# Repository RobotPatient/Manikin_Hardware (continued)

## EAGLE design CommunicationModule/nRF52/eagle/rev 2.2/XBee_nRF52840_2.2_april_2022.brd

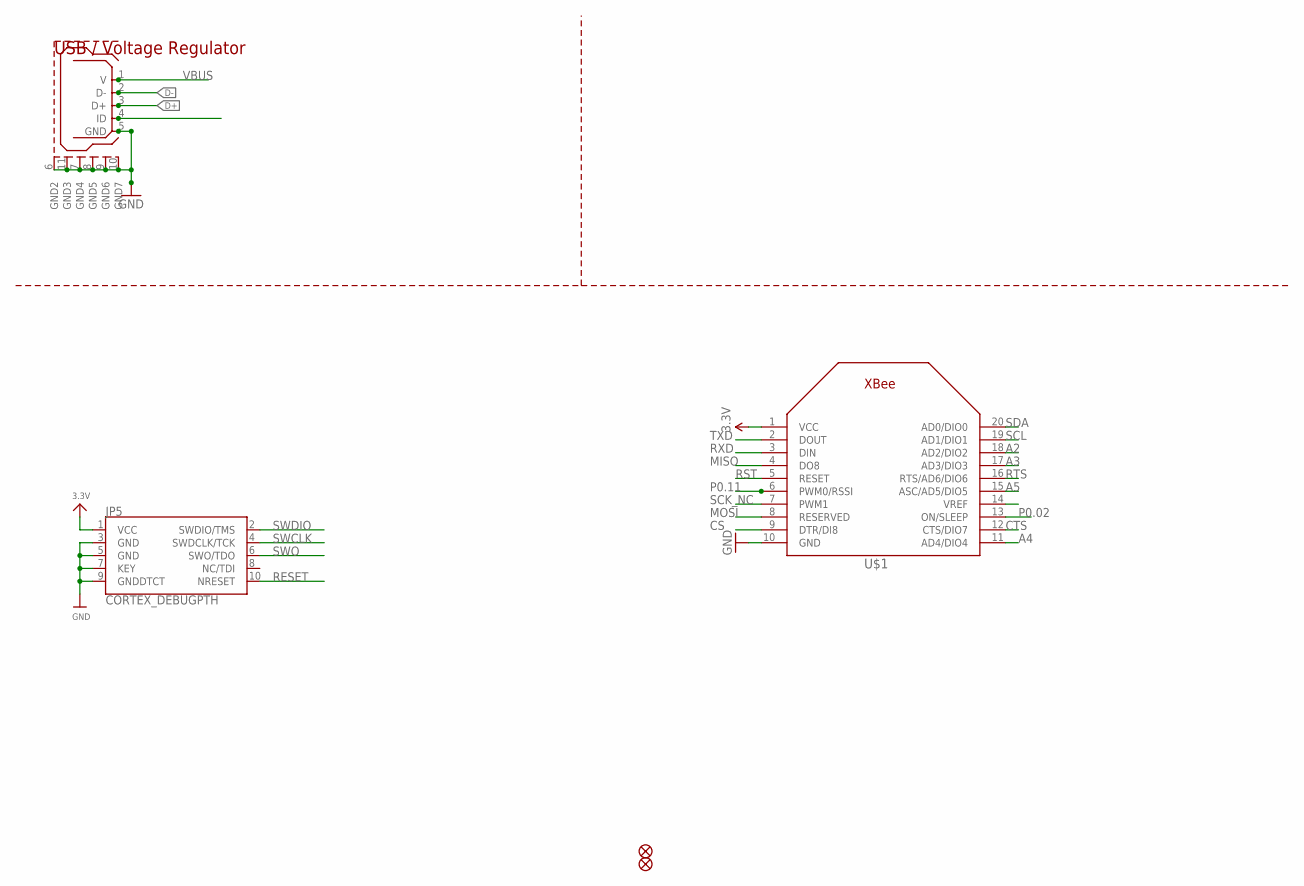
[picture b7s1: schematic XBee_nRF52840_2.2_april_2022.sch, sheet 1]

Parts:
FID1, FID3: FIDUCIAL_1MM
JP5: CORTEX_DEBUGPTH; 2X5-PTH-1.27MM
U$1: XBEE
U$2: USB_MICROB; USB_MICROB_PACKAGE

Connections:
3.3V: JP5.1 (VCC), U$1.1 (VCC); also elsewhere on the board
A2: U$1.18 (AD2/DIO2); also elsewhere on the board
A3: U$1.17 (AD3/DIO3); also elsewhere on the board
A4: U$1.11 (AD4/DIO4); also elsewhere on the board
A5: U$1.15 (ASC/AD5/DIO5); also elsewhere on the board
CS: U$1.9 (DTR/DI8)
CTS: U$1.12 (CTS/DIO7)
D+: U$2.3 (D+); also elsewhere on the board
D-: U$2.2 (D-); also elsewhere on the board
GND: JP5.3 (GND), JP5.5 (GND), JP5.7 (KEY), JP5.9 (GNDDTCT), U$1.10 (GND), U$2.5 (GND), U$2.6 (GND2), U$2.7 (GND4), U$2.8 (GND5), U$2.9 (GND6), U$2.10 (GND7), U$2.11 (GND3); also elsewhere on the board
MISO: U$1.4 (DO8); also elsewhere on the board
MOSI: U$1.8 (RESERVED); also elsewhere on the board
P0.02: U$1.13 (ON/SLEEP)
P0.11: U$1.6 (PWM0/RSSI)
RESET: JP5.10 (NRESET); also elsewhere on the board
RST: U$1.5 (RESET)
RTS: U$1.16 (RTS/AD6/DIO6)
RXD: U$1.3 (DIN); also elsewhere on the board
SCK_NC: U$1.7 (PWM1)
SCL: U$1.19 (AD1/DIO1); also elsewhere on the board
SDA: U$1.20 (AD0/DIO0); also elsewhere on the board
SWCLK: JP5.4 (SWDCLK/TCK); also elsewhere on the board
SWDIO: JP5.2 (SWDIO/TMS); also elsewhere on the board
SWO: JP5.6 (SWO/TDO); also elsewhere on the board
TXD: U$1.2 (DOUT); also elsewhere on the board
VBUS: U$2.1 (V); also elsewhere on the board

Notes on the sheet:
USB / Voltage Regulator

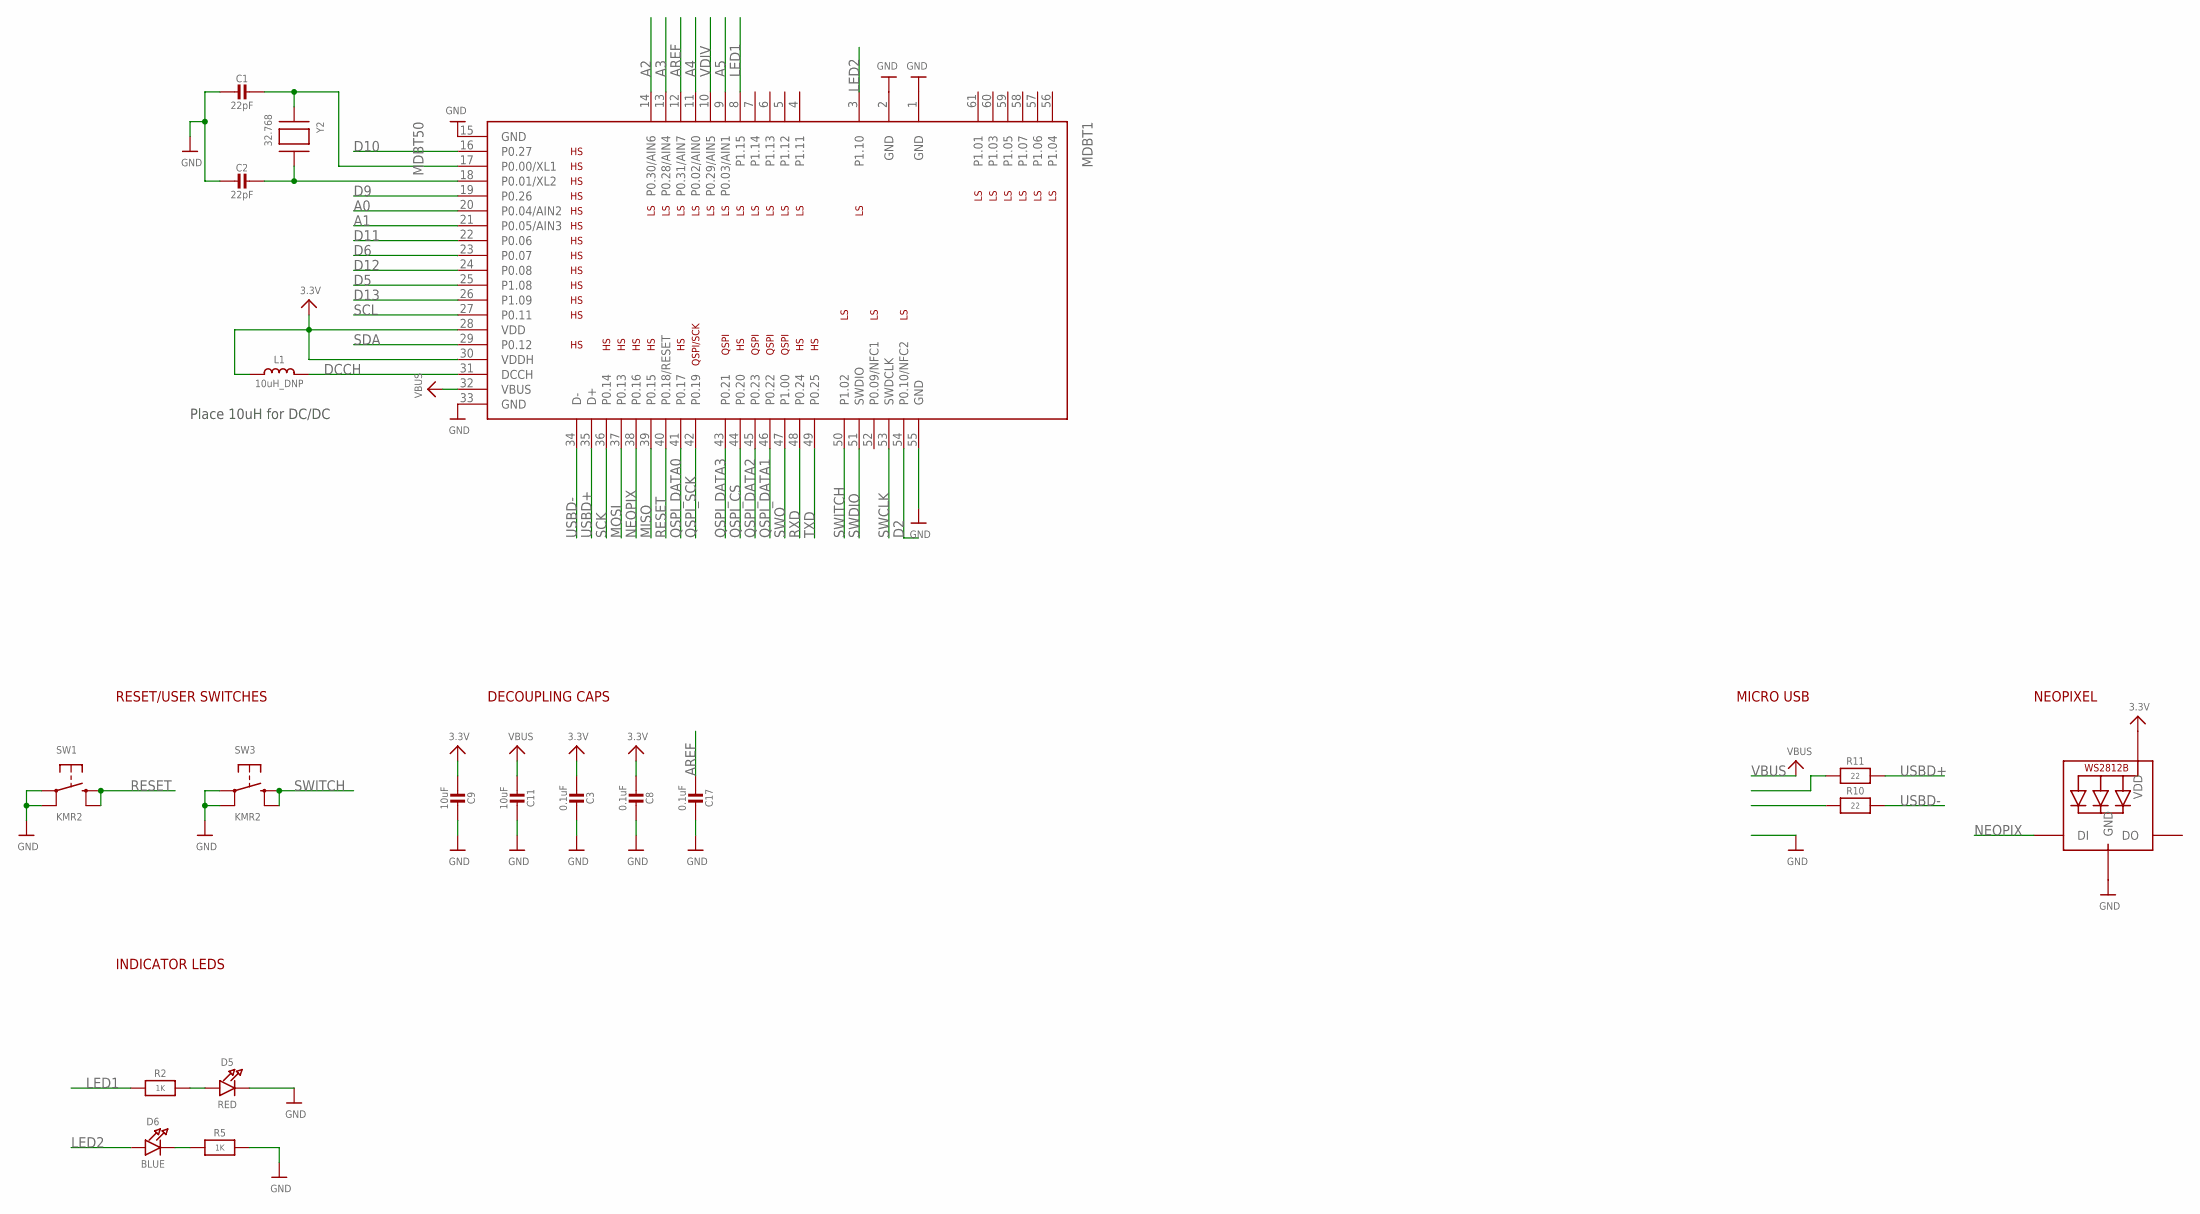
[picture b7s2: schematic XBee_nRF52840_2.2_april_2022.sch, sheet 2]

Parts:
C1, C2: 22pF; 0603-NO
C3, C8, C17: 0.1uF; 0603-NO
C9, C11: 10uF; 0805-NO
D5: RED; CHIPLED_0805_NOOUTLINE
D6: BLUE; CHIPLED_0805_NOOUTLINE
L1: 10uH_DNP; _0805MP
LED1: WS2812B3535; LED3535
MDBT1: MDBT50
R2, R5: 1K; 0603-NO
R10, R11: 22; 0603-NO
SW1, SW3: KMR2; BTN_KMR2_4.6X2.8
Y2: 32.768; XTAL3215

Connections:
3.3V: C3.2, C8.2, C9.2, L1.1, LED1.2 (VDD), MDBT1.28 (VDD), MDBT1.30 (VDDH); also elsewhere on the board
A0: MDBT1.20 (P0.04/AIN2)
A1: MDBT1.21 (P0.05/AIN3)
A2: MDBT1.14 (P0.30/AIN6); also elsewhere on the board
A3: MDBT1.13 (P0.28/AIN4); also elsewhere on the board
A4: MDBT1.11 (P0.02/AIN0); also elsewhere on the board
A5: MDBT1.9 (P0.03/AIN1); also elsewhere on the board
AREF: C17.2, MDBT1.12 (P0.31/AIN7)
D2: MDBT1.54 (P0.10/NFC2)
D5: MDBT1.25 (P1.08)
D6: MDBT1.23 (P0.07)
D9: MDBT1.19 (P0.26)
D10: MDBT1.16 (P0.27)
D11: MDBT1.22 (P0.06)
D12: MDBT1.24 (P0.08)
D13: MDBT1.26 (P1.09)
D+: R11.1; also elsewhere on the board
D-: R10.1; also elsewhere on the board
DCCH: L1.2, MDBT1.31 (DCCH)
GND: C1.2, C2.2, C3.1, C8.1, C9.1, C11.1, C17.1, D5.C, LED1.4 (GND), MDBT1.1 (GND), MDBT1.2 (GND), MDBT1.15 (GND), MDBT1.33 (GND), MDBT1.55 (GND), R5.2, SW1.A, SW1.A' (P1), SW3.A, SW3.A' (P1); also elsewhere on the board
LED1: MDBT1.8 (P1.15), R2.1
LED2: D6.A, MDBT1.3 (P1.10)
MISO: MDBT1.39 (P0.15); also elsewhere on the board
MOSI: MDBT1.37 (P0.13); also elsewhere on the board
unnamed: C1.1, MDBT1.17 (P0.00/XL1), Y2.P$1
unnamed: C2.1, MDBT1.18 (P0.01/XL2), Y2.P$2
unnamed: D6.C, R5.1
unnamed: D5.A, R2.2
NEOPIX: LED1.1 (DI), MDBT1.38 (P0.16)
QSPI_CS: MDBT1.44 (P0.20)
QSPI_DATA0: MDBT1.41 (P0.17)
QSPI_DATA1: MDBT1.46 (P0.22)
QSPI_DATA2: MDBT1.45 (P0.23)
QSPI_DATA3: MDBT1.43 (P0.21)
QSPI_SCK: MDBT1.42 (P0.19)
RESET: MDBT1.40 (P0.18/RESET), SW1.B (S), SW1.B' (S1); also elsewhere on the board
RXD: MDBT1.48 (P0.24); also elsewhere on the board
SCK: MDBT1.36 (P0.14)
SCL: MDBT1.27 (P0.11); also elsewhere on the board
SDA: MDBT1.29 (P0.12); also elsewhere on the board
SWCLK: MDBT1.53 (SWDCLK); also elsewhere on the board
SWDIO: MDBT1.51 (SWDIO); also elsewhere on the board
SWITCH: MDBT1.50 (P1.02), SW3.B (S), SW3.B' (S1)
SWO: MDBT1.47 (P1.00); also elsewhere on the board
TXD: MDBT1.49 (P0.25); also elsewhere on the board
USBD+: MDBT1.35 (D+), R11.2
USBD-: MDBT1.34 (D-), R10.2
VBUS: C11.2, MDBT1.32 (VBUS); also elsewhere on the board
VDIV: MDBT1.10 (P0.29/AIN5)

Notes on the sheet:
INDICATOR LEDS
RESET/USER SWITCHES
DECOUPLING CAPS
MICRO USB
NEOPIXEL
Place 10uH for DC/DC

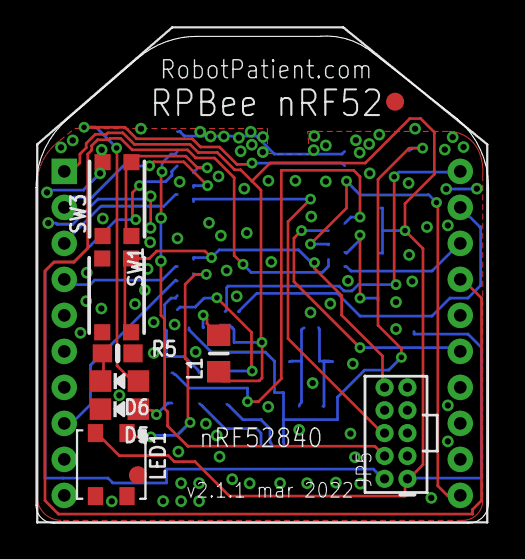
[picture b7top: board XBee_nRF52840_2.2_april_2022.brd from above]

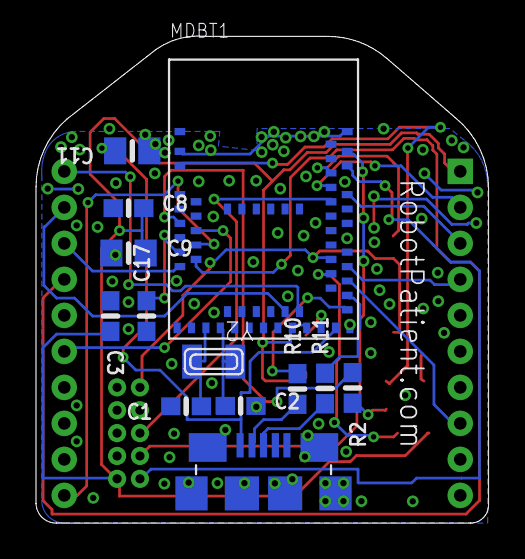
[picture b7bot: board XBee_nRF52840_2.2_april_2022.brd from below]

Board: 2 copper layers, 25.1 x 27.1 mm, 24 parts (13 on the bottom side), 31 nets.

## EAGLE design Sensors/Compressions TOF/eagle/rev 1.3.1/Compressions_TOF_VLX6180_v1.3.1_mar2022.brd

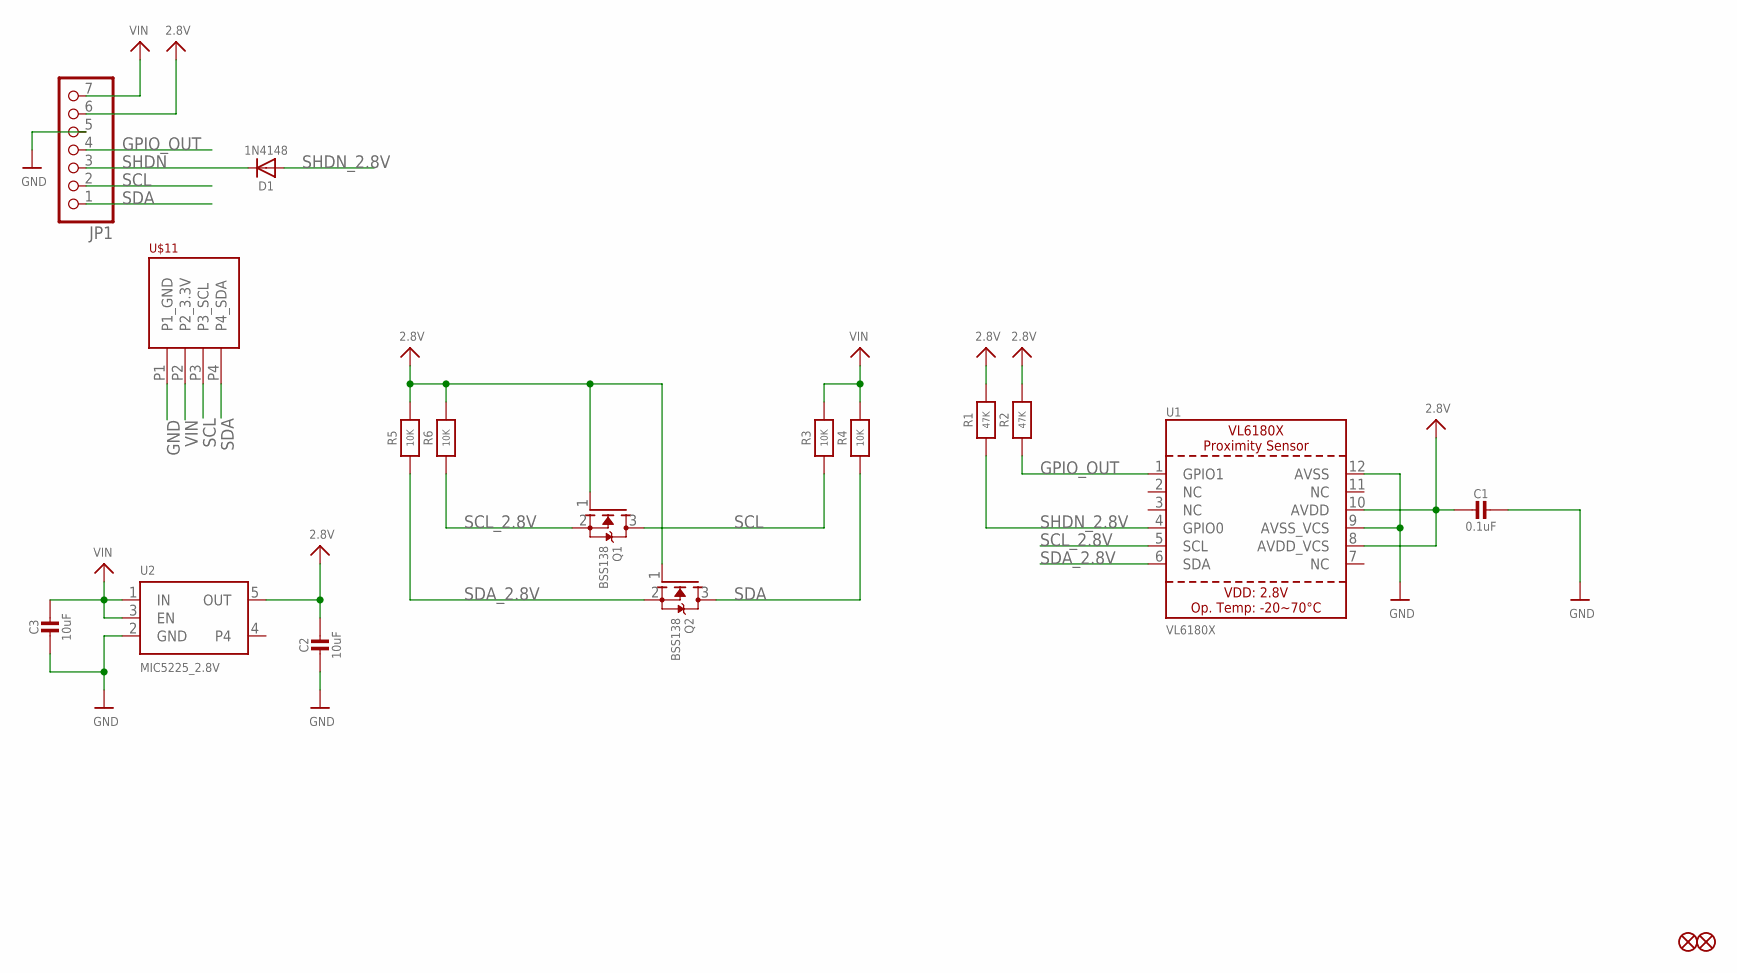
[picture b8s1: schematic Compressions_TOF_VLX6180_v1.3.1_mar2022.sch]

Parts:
C1: 0.1uF; 0805-NO
C2, C3: 10uF; 0805-NO
D1: 1N4148; SOD-323
FID1, FID2: FIDUCIAL""; FIDUCIAL_1MM
JP1: HEADER-1X770MIL; 1X07_ROUND_70
Q1, Q2: BSS138; SOT23-WIDE
R1, R2: 47K; 0805-NO
R3, R4, R5, R6: 10K; 0805-NO
U1: VL6180X; VL6180
U2: MIC5225_2.8V; SOT23-5
U$11: PHOENIX_PTSM_M4_THANGLE; PTSM_M4_TH

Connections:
2.8V: C1.2, C2.1, JP1.6, Q1.1 (G), Q2.1 (G), R1.2, R2.2, R5.2, R6.2, U1.8 (AVDD_VCS), U1.10 (AVDD), U2.5 (OUT)
GND: C1.1, C2.2, C3.2, JP1.5, U1.9 (AVSS_VCS), U1.12 (AVSS), U2.2 (GND), U$11.P1 (P1_GND)
GPIO_OUT: JP1.4, R2.1, U1.1 (GPIO1)
SCL: JP1.2, Q1.3 (D), R3.1, U$11.P3 (P3_SCL)
SCL_2.8V: Q1.2 (S), R6.1, U1.5 (SCL)
SDA: JP1.1, Q2.3 (D), R4.1, U$11.P4 (P4_SDA)
SDA_2.8V: Q2.2 (S), R5.1, U1.6 (SDA)
SHDN: D1.C, JP1.3
SHDN_2.8V: D1.A, R1.1, U1.4 (GPIO0)
VIN: C3.1, JP1.7, R3.2, R4.2, U2.1 (IN), U2.3 (EN), U$11.P2 (P2_3.3V)

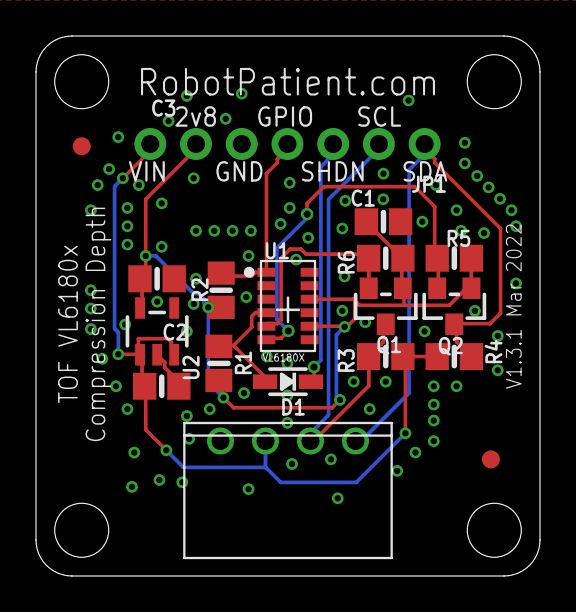
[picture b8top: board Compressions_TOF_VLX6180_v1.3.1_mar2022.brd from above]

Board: 2 copper layers, 28.0 x 30.0 mm, 18 parts (0 on the bottom side), 10 nets.

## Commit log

2023-02-05 -add files for Mainbord, SensorHub, ThoraxSensor and Bosch_BMI_BMM
2023-02-13 -add schematics for sensorhub rev 1.1 and rev 1.1.1
2023-02-13 -add schematic for mainbord
2023-02-13 -add schematic for bmi270 sensor
2023-02-13 -enh move mainbord schematic into folder with revision
2023-02-13 -add new design files for lite versions of actuatorhub and sensorhub
2023-02-13 -enh move pdf files to more sensible location
2023-02-13 -add pdf schematic for new sensorhub, actuatorhub and simbox
2023-02-15 -add eagle files for various sensors
2023-02-15 -add eagle files for Communication modules
2023-02-15 -add PDF schematic for sensors and communication modules
2023-02-17 -add ActuatorHub_Lite rev 1.1
2023-03-15 -add Rev 1.1.2 schematic, board and pdf of schematic
2023-05-11 Added Pro version for ActuatorHub with SRAM
2023-05-11 SoundHub Pro SAMD51 v1.0 added
2023-05-11 Added final version with BMM150 fix
2023-05-11 Update .gitignore
    -add .DS_Store files (Mac)
2023-05-11 -rm mac file
2023-05-11 restructured ActuatorHub
2023-05-11 -add PDF schematic for rev 1.0.1
2023-09-22 -add schematic for new powerhub
2023-09-23 -add new version with charger circuit
